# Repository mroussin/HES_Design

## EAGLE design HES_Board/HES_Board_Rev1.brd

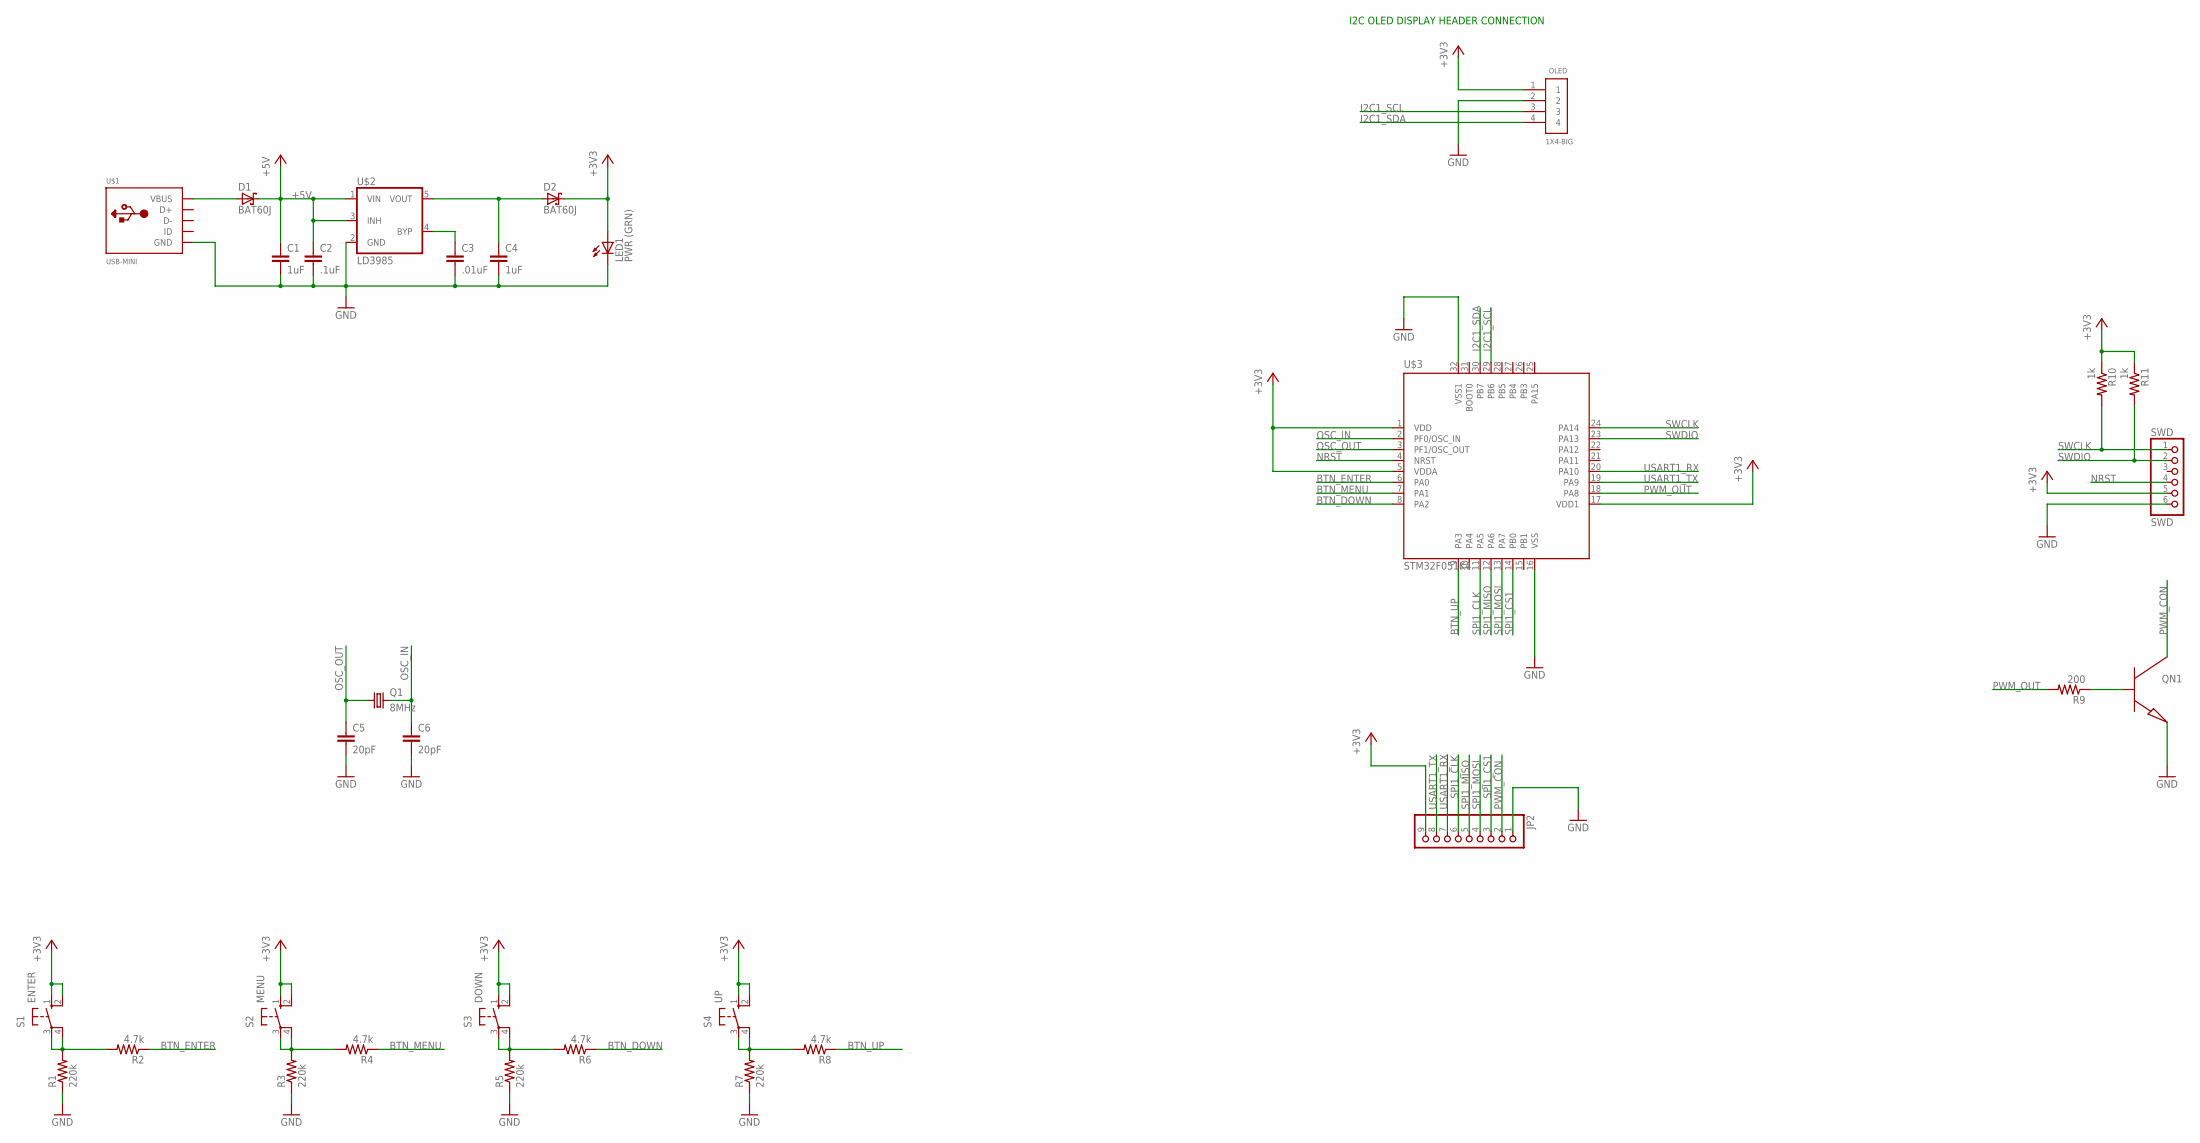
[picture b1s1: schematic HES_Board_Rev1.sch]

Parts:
C1, C4: 1uF; C0805
C2: .1uF; C0805
C3: .01uF; C0805
C5, C6: 20pF; C0805
D1, D2: BAT60J; SOD323_ST
JP2: PINHD-1X9; 1X09-BIG
LED1: PWR (GRN); CHIP-LED0805
OLED: 1X4-BIG; 1X04-BIG
Q1: 8MHz; HC49/S
QN1: NPN; SOT23
R1, R3, R5, R7: 220k; R0805
R2, R4, R6, R8: 4.7k; R0805
R9: 200; R0805
R10, R11: 1k; R0805
S1: ENTER; B3F-10XX
S2: MENU; B3F-10XX
S3: DOWN; B3F-10XX
S4: UP; B3F-10XX
SWD: SWD; 1X06-BIG
U$1: USB-MINI
U$2: LD3985; SOT23-5L
U$3: STM32F051K4; LQFP32-7X7

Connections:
+3V3: D2.C, JP2.9, LED1.A, OLED.1, R10.1, R11.1, S1.1 (S), S1.2 (S1), S2.1 (S), S2.2 (S1), S3.1 (S), S3.2 (S1), S4.1 (S), S4.2 (S1), SWD.5, U$3.1 (VDD), U$3.5 (VDDA), U$3.17 (VDD1)
+5V: C1.1, C2.1, D1.C, U$2.1 (VIN), U$2.3 (INH)
BTN_DOWN: R6.1, U$3.8 (PA2)
BTN_ENTER: R2.1, U$3.6 (PA0)
BTN_MENU: R4.1, U$3.7 (PA1)
BTN_UP: R8.1, U$3.9 (PA3)
GND: C1.2, C2.2, C3.2, C4.2, C5.2, C6.2, JP2.1, LED1.C, OLED.2, QN1.1 (E), R1.1, R3.1, R5.1, R7.1, SWD.6, U$1.GND, U$2.2 (GND), U$3.16 (VSS), U$3.32 (VSS1)
I2C1_SCL: OLED.3, U$3.29 (PB6)
I2C1_SDA: OLED.4, U$3.30 (PB7)
unnamed: D1.A, U$1.VBUS
unnamed: C4.1, D2.A, U$2.5 (VOUT)
unnamed: R5.2, R6.2, S3.3, S3.4 (P1)
unnamed: R1.2, R2.2, S1.3, S1.4 (P1)
unnamed: C3.1, U$2.4 (BYP)
unnamed: R7.2, R8.2, S4.3, S4.4 (P1)
unnamed: R3.2, R4.2, S2.3, S2.4 (P1)
unnamed: QN1.2 (B), R9.1
NRST: SWD.4, U$3.4 (NRST)
OSC_IN: C6.1, Q1.2, U$3.2 (PF0/OSC_IN)
OSC_OUT: C5.1, Q1.1, U$3.3 (PF1/OSC_OUT)
PWM_CON: JP2.2, QN1.3 (C)
PWM_OUT: R9.2, U$3.18 (PA8)
SPI1_CLK: JP2.6, U$3.11 (PA5)
SPI1_CS1: JP2.3, U$3.14 (PB0)
SPI1_MISO: JP2.5, U$3.12 (PA6)
SPI1_MOSI: JP2.4, U$3.13 (PA7)
SWCLK: R10.2, SWD.1, U$3.24 (PA14)
SWDIO: R11.2, SWD.2, U$3.23 (PA13)
USART1_RX: JP2.7, U$3.20 (PA10)
USART1_TX: JP2.8, U$3.19 (PA9)

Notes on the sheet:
I2C OLED DISPLAY HEADER CONNECTION

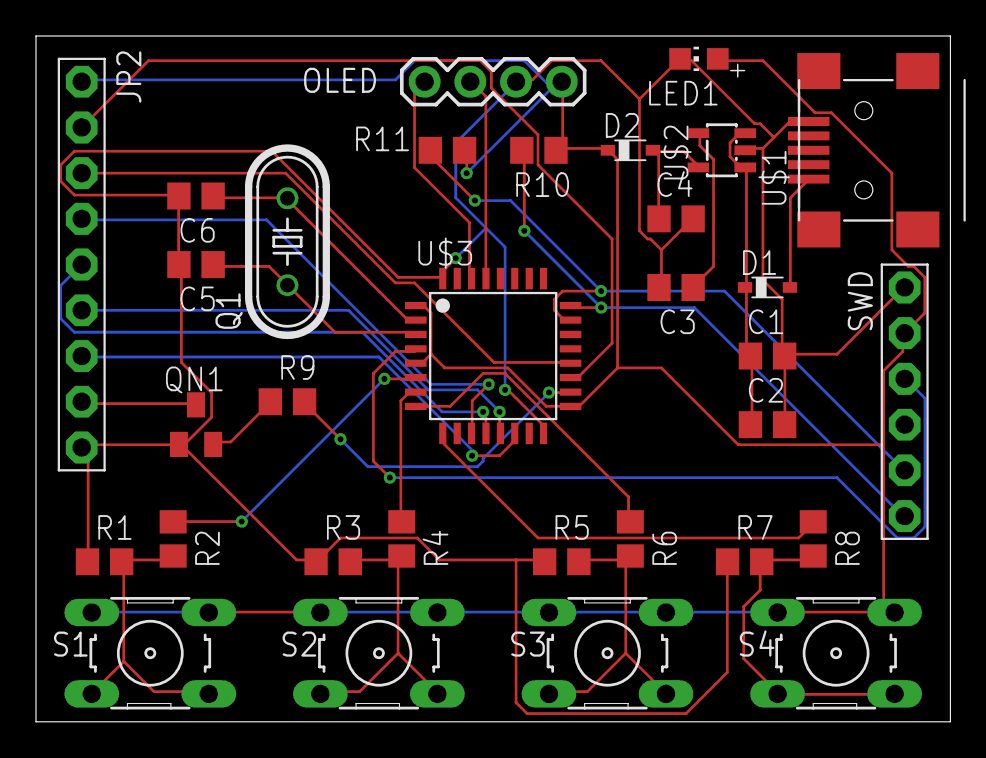
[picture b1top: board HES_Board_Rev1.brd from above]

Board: 2 copper layers, 50.8 x 38.1 mm, 32 parts (0 on the bottom side), 30 nets.

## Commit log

2015-08-30 :tada: Added .gitattributes & .gitignore files
2015-08-30 HES_Board_Rev1
    Original Board Design
